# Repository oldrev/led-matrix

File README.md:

# 蓝牙 LED 矩阵控制器

详情文档推荐使用 mkdocs 构建并查看。

构建文档需要先安装 Python3 及相关依赖：

```bash
$pip install --user -r requirements.txt
```

安装完成以后，执行：

```bash
$mkdocs serve
```

然后用浏览器打开`http://localhost:8000`即可。

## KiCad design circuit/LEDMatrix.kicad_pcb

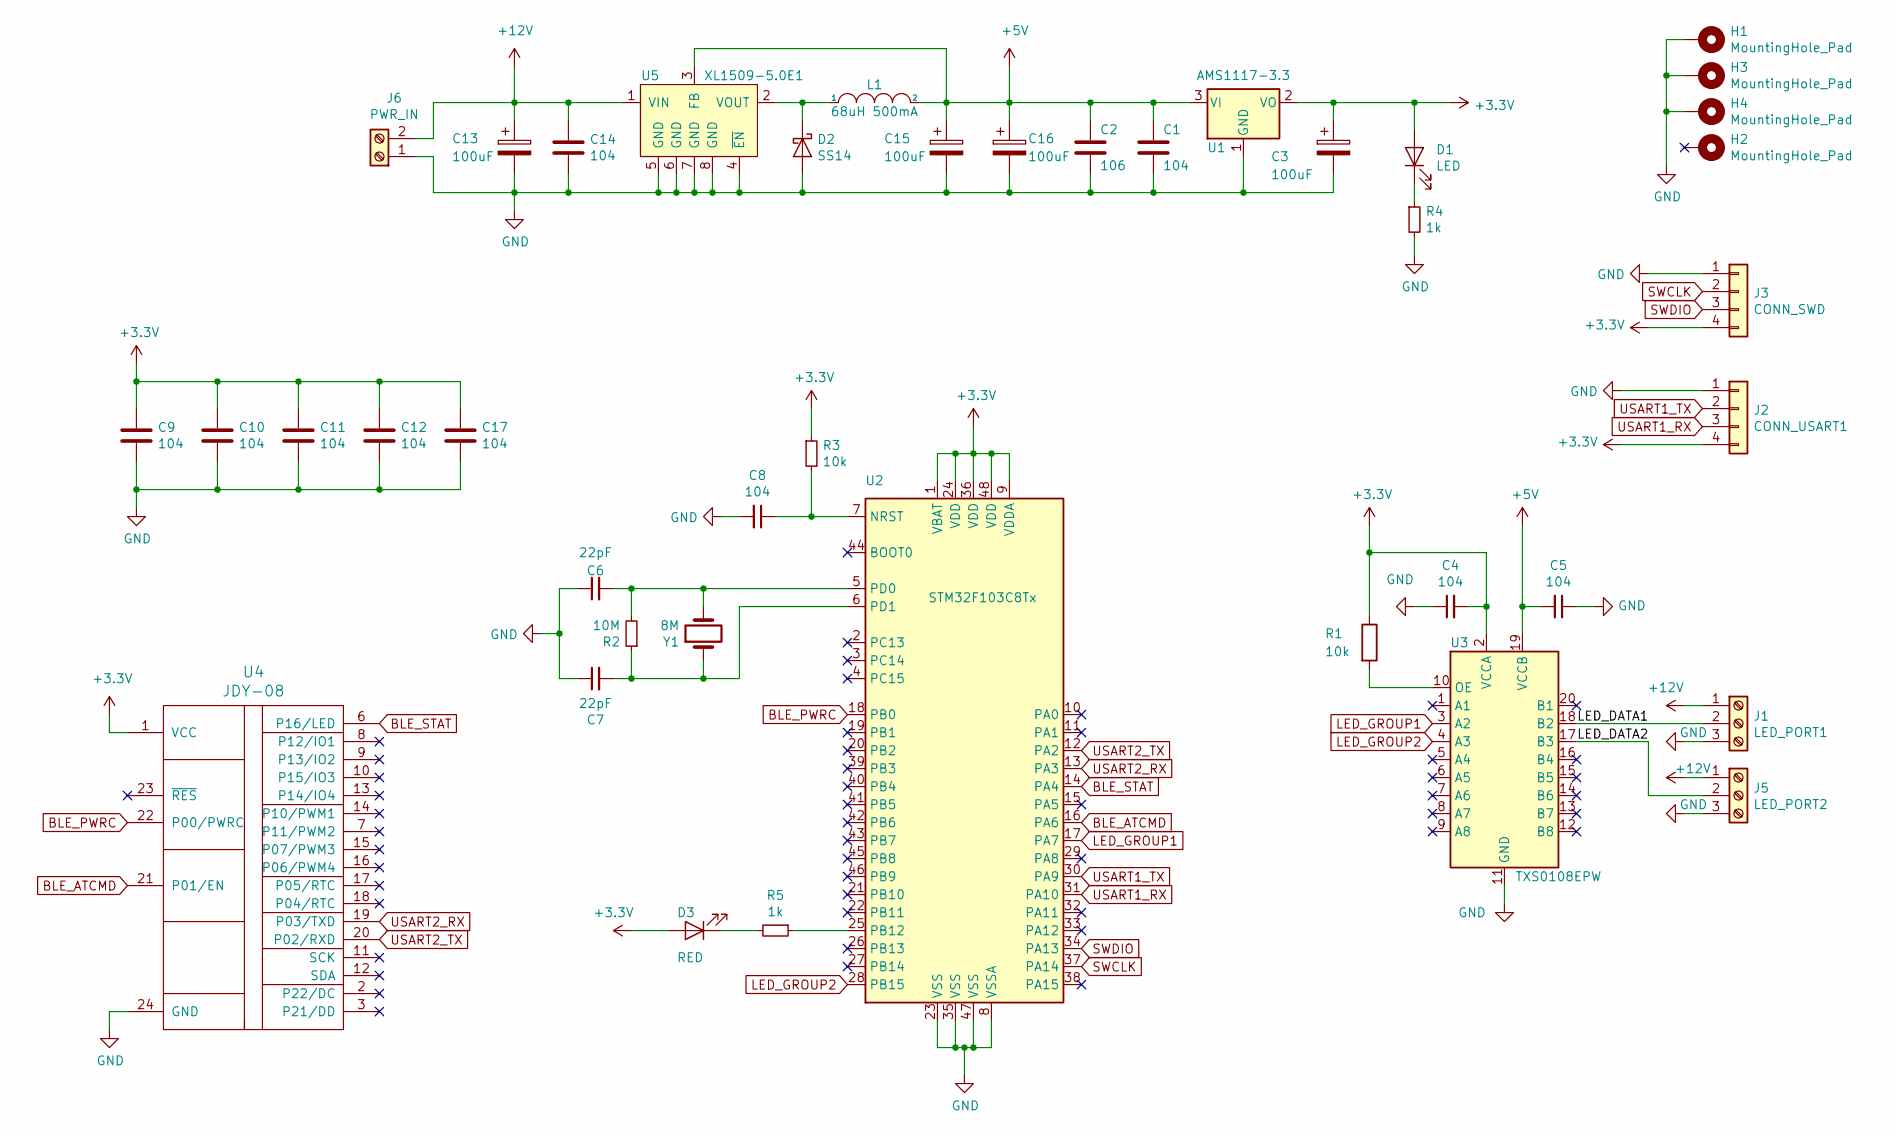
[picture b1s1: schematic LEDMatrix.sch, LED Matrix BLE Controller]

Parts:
C1, C4, C5, C8, C9, C10, C11, C12, C14, C17: 104; C_0603_1608Metric
C2: 106; C_0603_1608Metric; JLC_MODEL C19702
C3: 100uF; CP_EIA-3528-21_Kemet-B; JLC_MODEL TAJB107K006RNJ
C6, C7: 22pF; C_0603_1608Metric
C13, C15, C16: 100uF; CP_Elec_8x10; JLC_MODEL C134507
D1: LED; D_0603_1608Metric
D2: SS14; D_SMA
D3: RED; D_0603_1608Metric
H1, H2, H3, H4: MountingHole_Pad; MountingHole_3.2mm_M3_Pad_Via
J1: LED_PORT1; TerminalBlock_JL301-5.00-3P
J2: CONN_USART1; PinHeader_1x04_P2.54mm_Vertical
J3: CONN_SWD; PinHeader_1x04_P2.54mm_Vertical
J5: LED_PORT2; TerminalBlock_JL301-5.00-3P
J6: PWR_IN; TerminalBlock_JL301-5.00-2P
L1: 68uH 500mA; L_Taiyo-Yuden_NR-40xx_HandSoldering
R1, R3: 10k; C_0603_1608Metric
R2: 10M; C_0603_1608Metric
R4, R5: 1k; C_0603_1608Metric
U1: AMS1117-3.3; SOT-223-3_TabPin2; JLC_MODEL C6186
U2: STM32F103C8Tx; LQFP-48_7x7mm_P0.5mm
U3: TXS0108EPW; TSSOP-20_4.4x6.5mm_P0.65mm
U4: JDY-08; JDY-08_HandSoldering
U5: XL1509-5.0E1; SOIC-8_3.9x4.9mm_P1.27mm; JLC_MODEL C61063
Y1: 8M; Crystal_SMD_5032-2Pin_5.0x3.2mm; JLC_MODEL C115962

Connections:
+3V3: C3.1, C4.2, C9.1, C10.1, C11.1, C12.1, C17.1, D1.2 (A), D3.2 (A), J2.4, J3.4, R1.1, R3.1, U1.2 (VO), U2.1 (VBAT), U2.9 (VDDA), U2.24 (VDD), U2.36 (VDD), U2.48 (VDD), U3.2 (VCCA), U4.1 (VCC)
+5V: C1.1, C2.1, C5.2, C15.1, C16.1, L1.2, U1.3 (VI), U3.19 (VCCB), U5.3 (FB)
+12V: C13.1, C14.1, J1.1, J5.1, J6.2, U5.1 (VIN)
/LED_DATA1: J1.2, U3.18 (B2)
/LED_DATA2: J5.2, U3.17 (B3)
BLE_ATCMD: U2.16 (PA6), U4.21 (P01/EN)
BLE_PWRC: U2.18 (PB0), U4.22 (P00/PWRC)
BLE_STAT: U2.14 (PA4), U4.6 (P16/LED)
GND: C1.2, C2.2, C3.2, C4.1, C5.1, C6.1, C7.1, C8.2, C9.2, C10.2, C11.2, C12.2, C13.2, C14.2, C15.2, C16.2, C17.2, D2.2 (A), H1.1, H3.1, H4.1, J1.3, J2.1, J3.1, J5.3, J6.1, R4.2, U1.1 (GND), U2.8 (VSSA), U2.23 (VSS), U2.35 (VSS), U2.47 (VSS), U3.11 (GND), U4.24 (GND), U5.4 (~EN), U5.5 (GND), U5.6 (GND), U5.7 (GND), U5.8 (GND)
LED_GROUP1: U2.17 (PA7), U3.3 (A2)
LED_GROUP2: U2.28 (PB15), U3.4 (A3)
unnamed: C6.2, R2.2, U2.5 (PD0), Y1.2
unnamed: C7.2, R2.1, U2.6 (PD1), Y1.1
unnamed: C8.1, R3.2, U2.7 (NRST)
unnamed: D1.1 (K), R4.1
unnamed: D2.1 (K), L1.1, U5.2 (VOUT)
unnamed: D3.1 (K), R5.2
unnamed: R1.2, U3.10 (OE)
unnamed: R5.1, U2.25 (PB12)
SWCLK: J3.2, U2.37 (PA14)
SWDIO: J3.3, U2.34 (PA13)
USART1_RX: J2.3, U2.31 (PA10)
USART1_TX: J2.2, U2.30 (PA9)
USART2_RX: U2.13 (PA3), U4.19 (P03/TXD)
USART2_TX: U2.12 (PA2), U4.20 (P02/RXD)

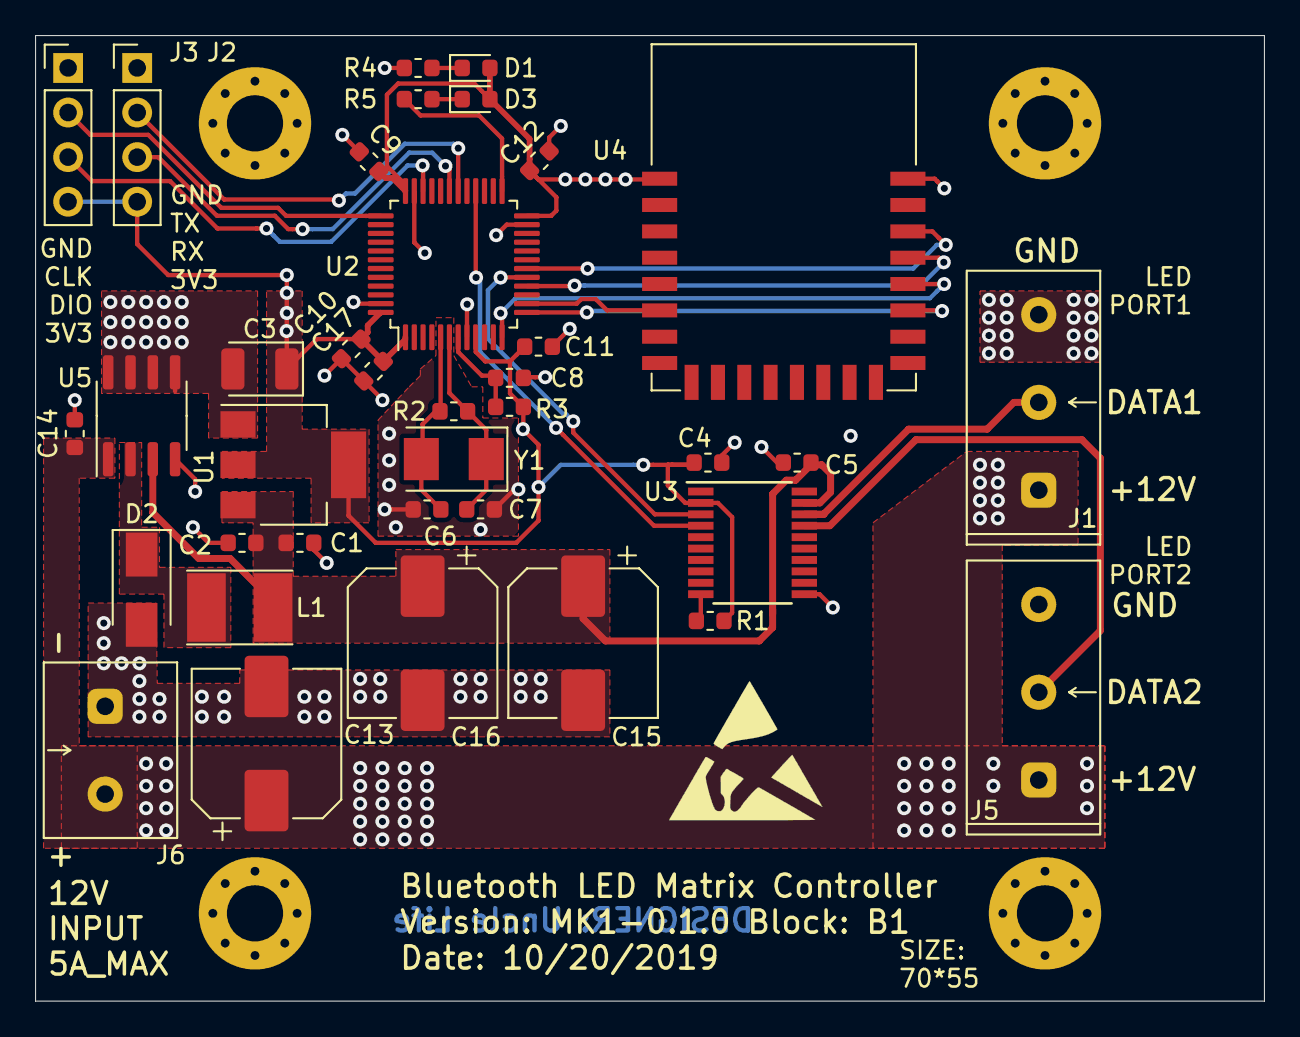
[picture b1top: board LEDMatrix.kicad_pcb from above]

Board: 2 copper layers, 70.0 x 55.0 mm, 41 parts (0 on the bottom side), 25 nets.

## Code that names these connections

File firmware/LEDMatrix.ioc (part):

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Mcu.Name=STM32F103C(8-B)Tx
Mcu.Package=LQFP48
Mcu.UserName=STM32F103C8Tx
PA10.Mode=Asynchronous
PA10.Signal=USART1_RX
PA13.Mode=Serial_Wire
PA13.Signal=SYS_JTMS-SWDIO
PA14.Mode=Serial_Wire
PA14.Signal=SYS_JTCK-SWCLK
PA2.Mode=Asynchronous
PA2.Signal=USART2_TX
PA3.Mode=Asynchronous
PA3.Signal=USART2_RX
PA4.GPIOParameters=GPIO_PuPd,GPIO_Label,GPIO_Mode
PA4.GPIO_Label=BLE_STAT
PA4.GPIO_Mode=GPIO_MODE_INPUT
PA4.GPIO_PuPd=GPIO_NOPULL
PA4.Signal=GPIO_Input
PA5.GPIOParameters=GPIO_Speed,GPIO_Mode
PA5.GPIO_Mode=GPIO_MODE_AF_PP
PA5.GPIO_Speed=GPIO_SPEED_FREQ_HIGH
PA5.Mode=TX_Only_Simplex_Unidirect_Master
PA5.Signal=SPI1_SCK
PA6.GPIOParameters=GPIO_Speed,PinState,GPIO_PuPd,GPIO_Label,GPIO_ModeDefaultOutputPP
PA6.GPIO_Label=BLE_ATCMD
PA6.GPIO_ModeDefaultOutputPP=GPIO_MODE_OUTPUT_PP
PA6.GPIO_PuPd=GPIO_NOPULL
PA6.GPIO_Speed=GPIO_SPEED_FREQ_LOW
PA6.PinState=GPIO_PIN_RESET
PA6.Signal=GPIO_Output
PA7.GPIOParameters=GPIO_Speed,GPIO_Mode
PA7.GPIO_Mode=GPIO_MODE_AF_PP
PA7.GPIO_Speed=GPIO_SPEED_FREQ_HIGH
PA7.Mode=TX_Only_Simplex_Unidirect_Master
PA7.Signal=SPI1_MOSI
PA9.Mode=Asynchronous
PA9.Signal=USART1_TX
PB0.GPIOParameters=GPIO_Speed,PinState,GPIO_PuPd,GPIO_Label,GPIO_ModeDefaultOutputPP
PB0.GPIO_Label=BLE_PWRC
PB0.GPIO_ModeDefaultOutputPP=GPIO_MODE_OUTPUT_PP
PB0.GPIO_PuPd=GPIO_NOPULL
PB0.GPIO_Speed=GPIO_SPEED_FREQ_LOW
PB0.PinState=GPIO_PIN_RESET
PB0.Signal=GPIO_Output
PB12.GPIOParameters=GPIO_Speed,PinState,GPIO_PuPd,GPIO_Label,GPIO_ModeDefaultOutputPP
PB12.GPIO_Label=DBG_LED
PB12.GPIO_ModeDefaultOutputPP=GPIO_MODE_OUTPUT_PP
PB12.GPIO_PuPd=GPIO_NOPULL
PB12.GPIO_Speed=GPIO_SPEED_FREQ_LOW
PB12.PinState=GPIO_PIN_RESET
PB12.Signal=GPIO_Output
PB13.GPIOParameters=GPIO_Speed,GPIO_Mode
PB13.GPIO_Mode=GPIO_MODE_AF_PP
PB13.GPIO_Speed=GPIO_SPEED_FREQ_HIGH
PB13.Mode=TX_Only_Simplex_Unidirect_Master
PB13.Signal=SPI2_SCK
PB15.GPIOParameters=GPIO_Speed,GPIO_Mode
PB15.GPIO_Mode=GPIO_MODE_AF_PP
PB15.GPIO_Speed=GPIO_SPEED_FREQ_HIGH
PB15.Mode=TX_Only_Simplex_Unidirect_Master
PB15.Signal=SPI2_MOSI
PD0-OSC_IN.Mode=HSE-External-Oscillator
PD0-OSC_IN.Signal=RCC_OSC_IN
PD1-OSC_OUT.Mode=HSE-External-Oscillator
PD1-OSC_OUT.Signal=RCC_OSC_OUT
RCC.SYSCLKFreq_VALUE=56000000
RCC.SYSCLKSource=RCC_SYSCLKSOURCE_PLLCLK
board=custom

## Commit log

2019-11-02 初次提交
2019-11-02 完善文档
2019-11-02 完善分包处理
2019-11-04 文档更新
2019-11-04 重新调整文档个是
2019-11-04 完善 README
2019-11-04 解决文档错误
2019-11-04 文档调整，增加色盘颜色
2019-11-04 增加外壳图纸
2019-11-05 完善小程序
2019-11-07 增加显示配置的协议说明
2019-11-07 增加复位功能
2019-11-07 解决发送快了会闪烁的 bug
2019-11-07 解决 release 无法编译的问题
2019-11-07 增加恢复出厂设置功能
2019-11-08 代码优化
2020-08-25 更新方法
2020-08-25 增加检查是否开启广播的功能
2020-08-26 更新名称
2020-08-26 更新框架文档等
2020-08-26 更新文档
2020-08-26 调整灯珠参数
2020-08-27 修复显示 bug
